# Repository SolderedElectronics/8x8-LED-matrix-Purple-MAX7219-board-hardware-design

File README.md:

# 8x8 LED matrix Purple MAX7219 board Hardware Design

## About the Product

|  |
| :----------------------------------------------------------: |
| [Buy 8x8 LED matrix Purple MAX7219 board](https://www.solde.red/333150) |

The LED matrix 8×8 is a system of 64 interconnected LEDs that, with the help of the MAX7219 LED driver, light up as programmed, and all of this is located on one board and is truly easy to use. You can use them to show letters or symbols, display text, and the like. It is possible to connect several modules with just a few wires and control several matrices at once.

The design of the modules is such that they will look like they are from one piece, even if you stack several of them one after the other. The LEDs on the board are beautiful 0402 very small LEDs and give a very nice effect when lit.

---

## Repository Contents

This repository contains all design files for 8x8 LED matrix Purple MAX7219 board, organized as follows:

- **`CAD` folder**: Contains KiCAD design files, including:
  - Schematics
  - PCB layout
  - Panel PCB layout
  - Source 3D files in Fusion360, if any
  - All files are sorted by version with a detailed change log.
- **`OUTPUTS` folder**: Includes all production-ready files, such as:
  - Bill of Materials (BOM) and interactive BOM (iBOM)
  - PDF versions of schematics
  - 3D `.step` file of the board
  - 3D-printable models
  - Gerber files for PCB manufacturing
  - Image of the pinout of the board
  - Product image
  - Compliance, legal and generic sales documents

Refer to the `Change Log` in the CAD folder for details about updates between versions.

---

## Learn More About the Product

Beyond the repository, explore the following resources:

### Soldered Verify

The **Soldered Verify** system ensures every board you purchase from Soldered is fully functional. It also provides access to exclusive test data for your product. To get started, find the unique Soldered Verify ID on your product's packaging and enter the ID on the [Soldered Verify page](https://soldered.com/verify/) to access test results and additional product details.

### Soldered Community

Soldered Community is your go-to place for technical support. Our engineers track and answer all questions posted there, and it’s a great space for the maker community. Get answers to your questions and solutions for your challenges at [Soldered Community](https://soldered.com/community).

### solde.red

solde.red is an ultimate URL shortener and information hub. Access it by typing solde.red/ followed by your product SKU, e.g., [solde.red/333000](https://solde.red/333000), to find getting-started guides, datasheets, open-source hardware and software files, certifications, images, pinouts, and more. Read more about the shortener [here](https://solde.red/info/).

---

## Contributing

Contributions are welcome! Here’s how you can get involved:

- Submit pull requests to enhance the design or fix issues.
- Report bugs or problems by opening an issue.

We encourage community collaboration to make this product even better.

---

## About Soldered

[Soldered for Makers](https://soldered.com) specializes in designing and manufacturing electronic products tailored for enthusiasts, ranging from hobbyists to professionals. Our portfolio includes electronic boards, sensors, and actuators that are widely utilized in fields such as microelectronics, mechatronics, robotics, programming, and IoT. Every product we offer is designed in-house and built upon open-source hardware and software platforms. Proudly certified and manufactured within the European Union, our catalog likely includes the product you need for your project.

We complement these products with comprehensive tutorials and manuals, product descriptions, schematics, programming codes, and project examples. Our round-the-clock [customer and technical support](https://soldered.com/community) is available for all our products, irrespective of the sales channel. Soldered’s success and services reflect our maker community’s unwavering [trust](https://www.trustpilot.com/review/soldered.com), for which we are deeply grateful. Join our community and create using Soldered products.

---

## License

All Soldered open-source hardware (OSH) is under The TAPR Open Hardware License. Read more in the LICENSE file located in this repository.

**Disclaimer:**

No warranty - all designs in this repository are distributed in the hope that they will be useful, but without any warranty. They are provided "AS IS", therefore without warranty of any kind, either expressed or implied. The entire quality and performance of what you do with the contents of this repository are your responsibility. In no event Soldered Electronics will be liable for your damages, or losses, including any general, special, incidental, or consequential damage arising out of the use or inability to use the contents of this repository. 

---

## Have fun!

Thank you for your support from your fellow makers at Soldered Electronics.

Happy Making!

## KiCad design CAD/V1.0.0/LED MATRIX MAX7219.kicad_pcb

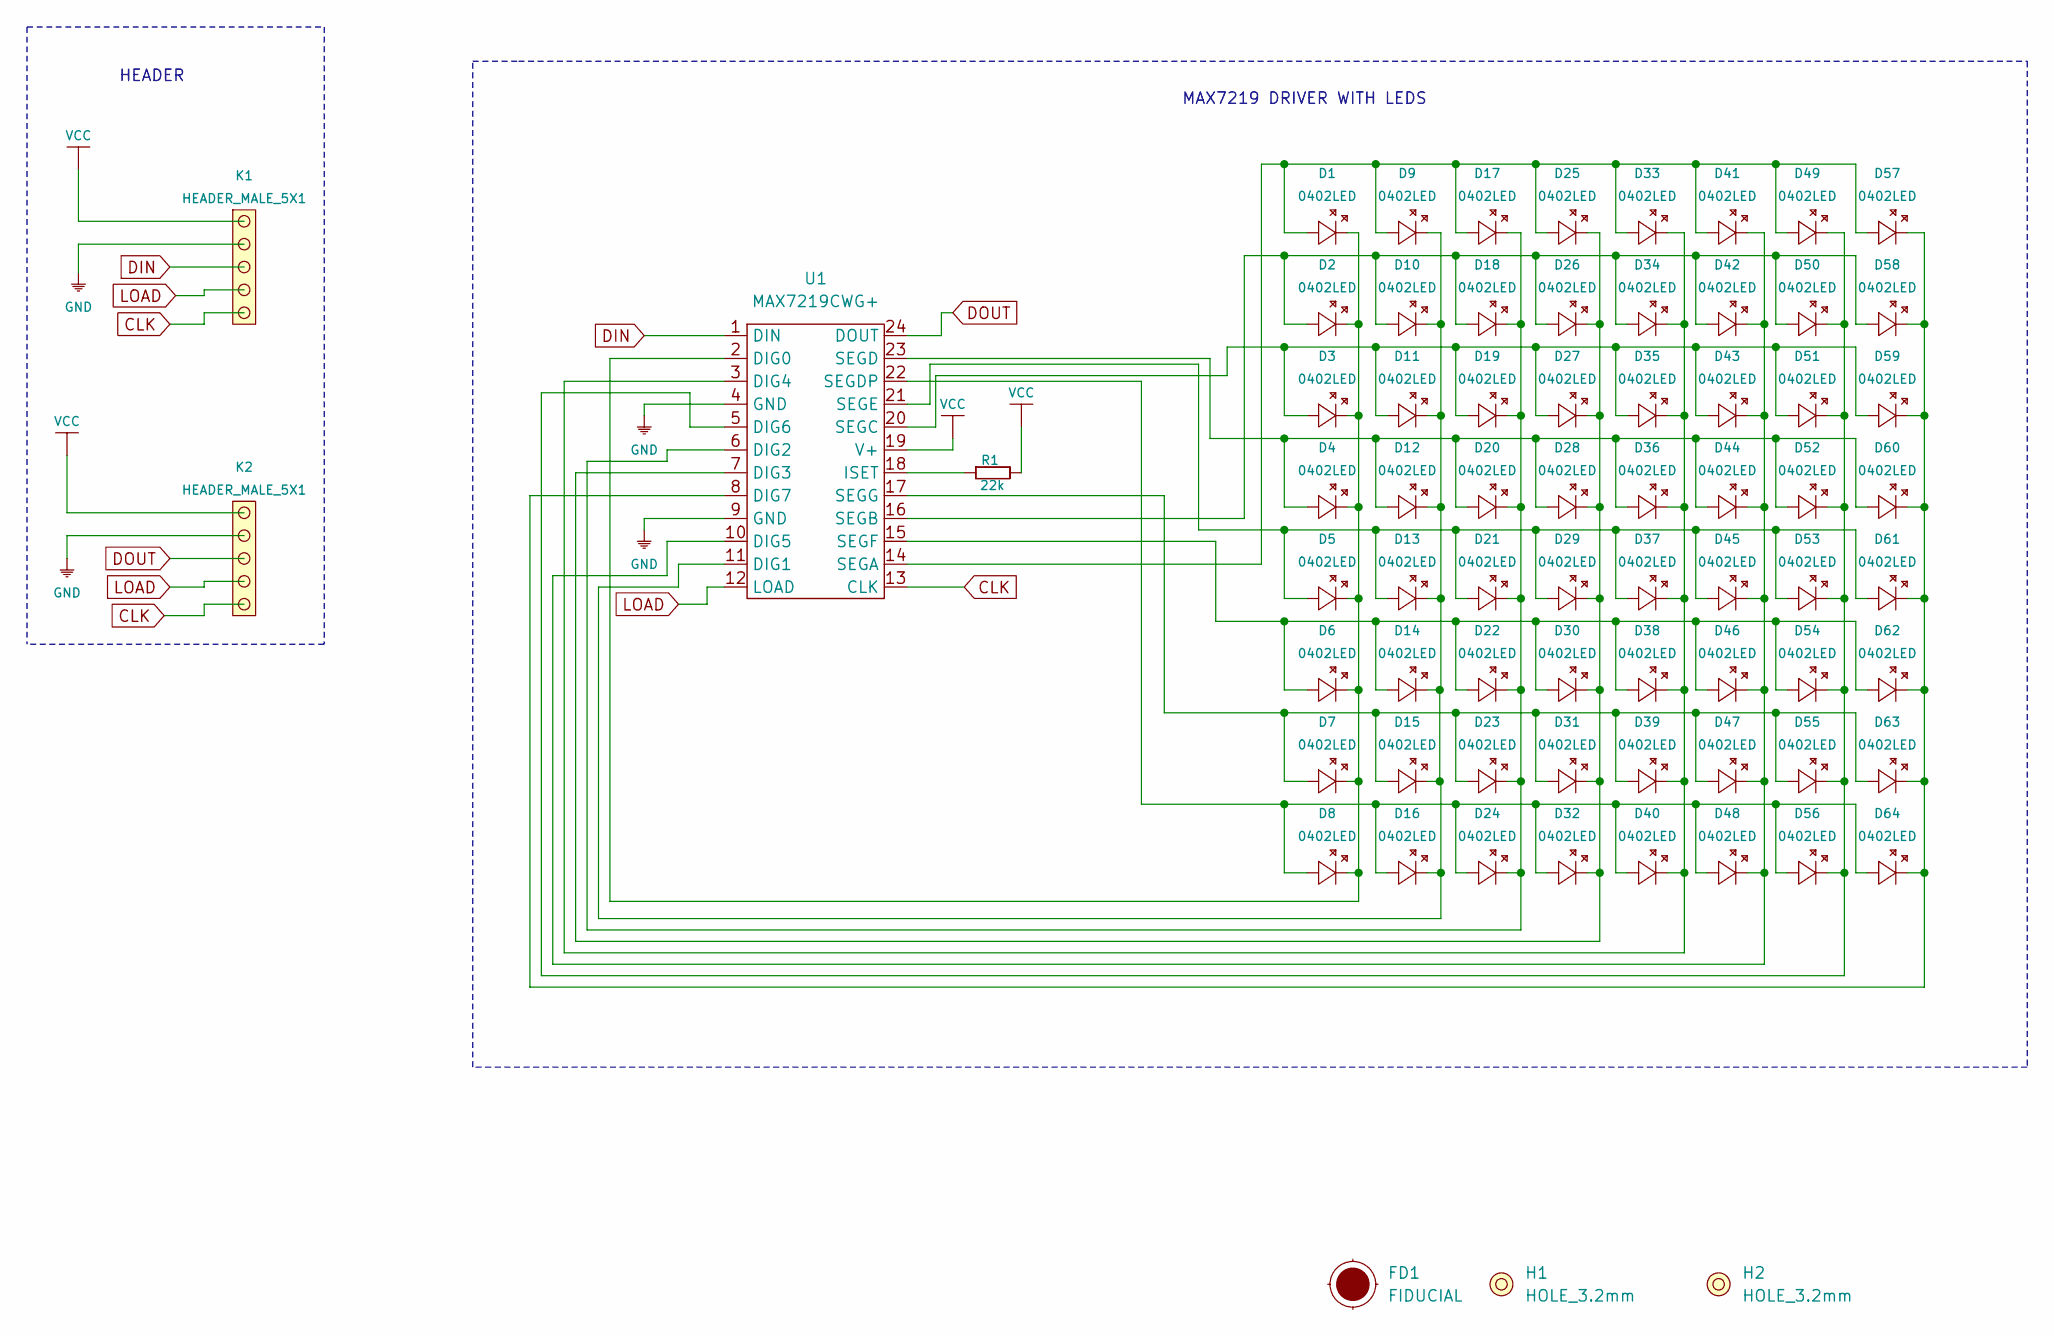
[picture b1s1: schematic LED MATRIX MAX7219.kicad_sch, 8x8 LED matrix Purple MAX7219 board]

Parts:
D1, D2, D3, D4, D5, D6, D7, D8, D9, D10, D11, D12, D13, D14, D15, D16, D17, D18, D19, D20, D21, D22, D23, D24, D25, D26, D27, D28, D29, D30, D31, D32, D33, D34, D35, D36, D37, D38, D39, D40, D41, D42, D43, D44, D45, D46, D47, D48, D49, D50, D51, D52, D53, D54, D55, D56, D57, D58, D59, D60, D61, D62, D63, D64: 0402LED
FD1: FIDUCIAL; FIDUCIAL_23
H1, H2: HOLE_3.2mm
K1, K2: HEADER_MALE_5X1
R1: 22k; 0603R
U1: MAX7219CWG+; SOIC-24

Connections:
CLK: K1.1, K2.1, U1.13 (CLK)
DIN: K1.3, U1.1 (DIN)
DOUT: K2.3, U1.24 (DOUT)
GND: K1.4, K2.4, U1.4 (GND), U1.9 (GND)
LOAD: K1.2, K2.2, U1.12 (LOAD)
unnamed: D1.1 (A), D9.1 (A), D17.1 (A), D25.1 (A), D33.1 (A), D41.1 (A), D49.1 (A), D57.1 (A), U1.14 (SEGA)
unnamed: D1.2 (K), D2.2 (K), D3.2 (K), D4.2 (K), D5.2 (K), D6.2 (K), D7.2 (K), D8.2 (K), U1.2 (DIG0)
unnamed: D2.1 (A), D10.1 (A), D18.1 (A), D26.1 (A), D34.1 (A), D42.1 (A), D50.1 (A), D58.1 (A), U1.16 (SEGB)
unnamed: D9.2 (K), D10.2 (K), D11.2 (K), D12.2 (K), D13.2 (K), D14.2 (K), D15.2 (K), D16.2 (K), U1.11 (DIG1)
unnamed: D3.1 (A), D11.1 (A), D19.1 (A), D27.1 (A), D35.1 (A), D43.1 (A), D51.1 (A), D59.1 (A), U1.20 (SEGC)
unnamed: D4.1 (A), D12.1 (A), D20.1 (A), D28.1 (A), D36.1 (A), D44.1 (A), D52.1 (A), D60.1 (A), U1.23 (SEGD)
unnamed: D5.1 (A), D13.1 (A), D21.1 (A), D29.1 (A), D37.1 (A), D45.1 (A), D53.1 (A), D61.1 (A), U1.21 (SEGE)
unnamed: D6.1 (A), D14.1 (A), D22.1 (A), D30.1 (A), D38.1 (A), D46.1 (A), D54.1 (A), D62.1 (A), U1.15 (SEGF)
unnamed: D7.1 (A), D15.1 (A), D23.1 (A), D31.1 (A), D39.1 (A), D47.1 (A), D55.1 (A), D63.1 (A), U1.17 (SEGG)
unnamed: D8.1 (A), D16.1 (A), D24.1 (A), D32.1 (A), D40.1 (A), D48.1 (A), D56.1 (A), D64.1 (A), U1.22 (SEGDP)
unnamed: D17.2 (K), D18.2 (K), D19.2 (K), D20.2 (K), D21.2 (K), D22.2 (K), D23.2 (K), D24.2 (K), U1.6 (DIG2)
unnamed: D25.2 (K), D26.2 (K), D27.2 (K), D28.2 (K), D29.2 (K), D30.2 (K), D31.2 (K), D32.2 (K), U1.7 (DIG3)
unnamed: D33.2 (K), D34.2 (K), D35.2 (K), D36.2 (K), D37.2 (K), D38.2 (K), D39.2 (K), D40.2 (K), U1.3 (DIG4)
unnamed: D41.2 (K), D42.2 (K), D43.2 (K), D44.2 (K), D45.2 (K), D46.2 (K), D47.2 (K), D48.2 (K), U1.10 (DIG5)
unnamed: D49.2 (K), D50.2 (K), D51.2 (K), D52.2 (K), D53.2 (K), D54.2 (K), D55.2 (K), D56.2 (K), U1.5 (DIG6)
unnamed: D57.2 (K), D58.2 (K), D59.2 (K), D60.2 (K), D61.2 (K), D62.2 (K), D63.2 (K), D64.2 (K), U1.8 (DIG7)
unnamed: R1.1, U1.18 (ISET)
VCC: K1.5, K2.5, R1.2, U1.19 (V+)

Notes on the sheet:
HEADER
MAX7219 DRIVER WITH LEDS

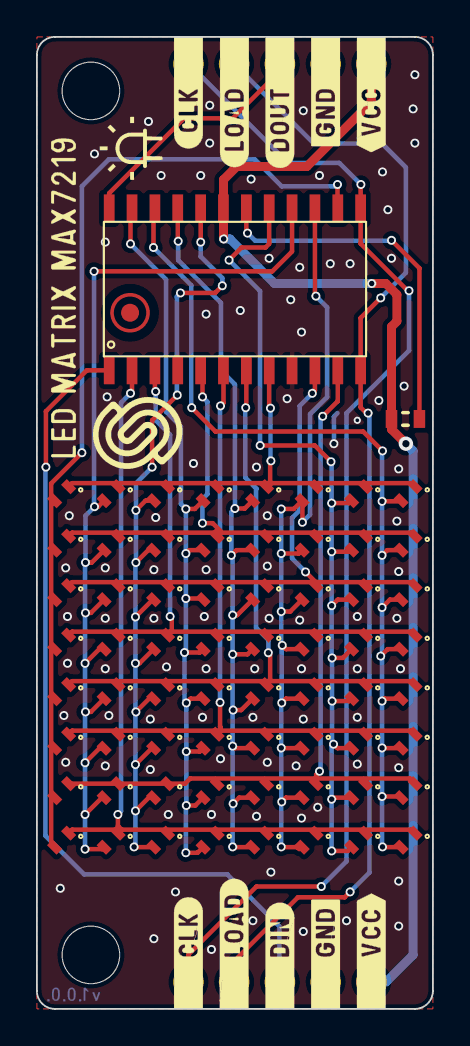
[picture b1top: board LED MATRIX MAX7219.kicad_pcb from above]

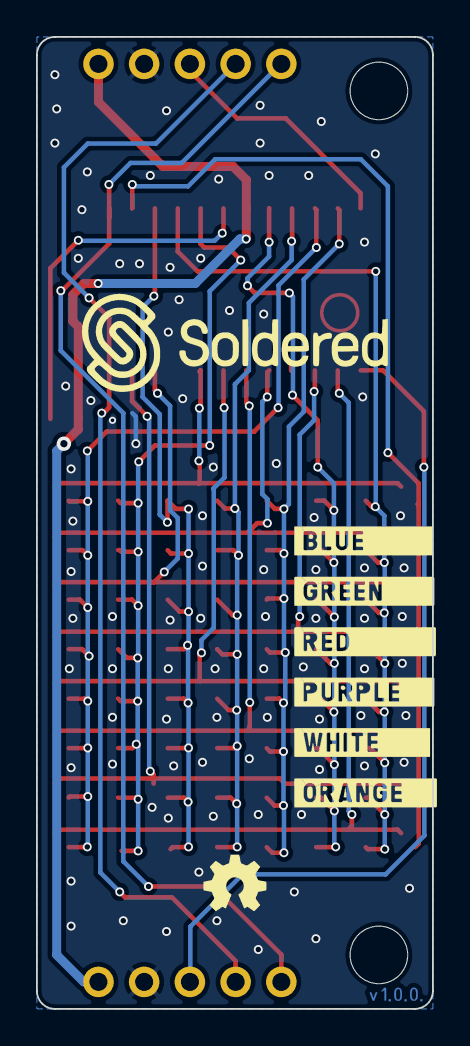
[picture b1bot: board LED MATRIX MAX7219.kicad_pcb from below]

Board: 2 copper layers, 22.0 x 54.0 mm, 72 parts (3 on the bottom side), 23 nets.

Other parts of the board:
Ref**: Val**; Version1.0.0.

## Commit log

2022-08-06 Updating open source files.
